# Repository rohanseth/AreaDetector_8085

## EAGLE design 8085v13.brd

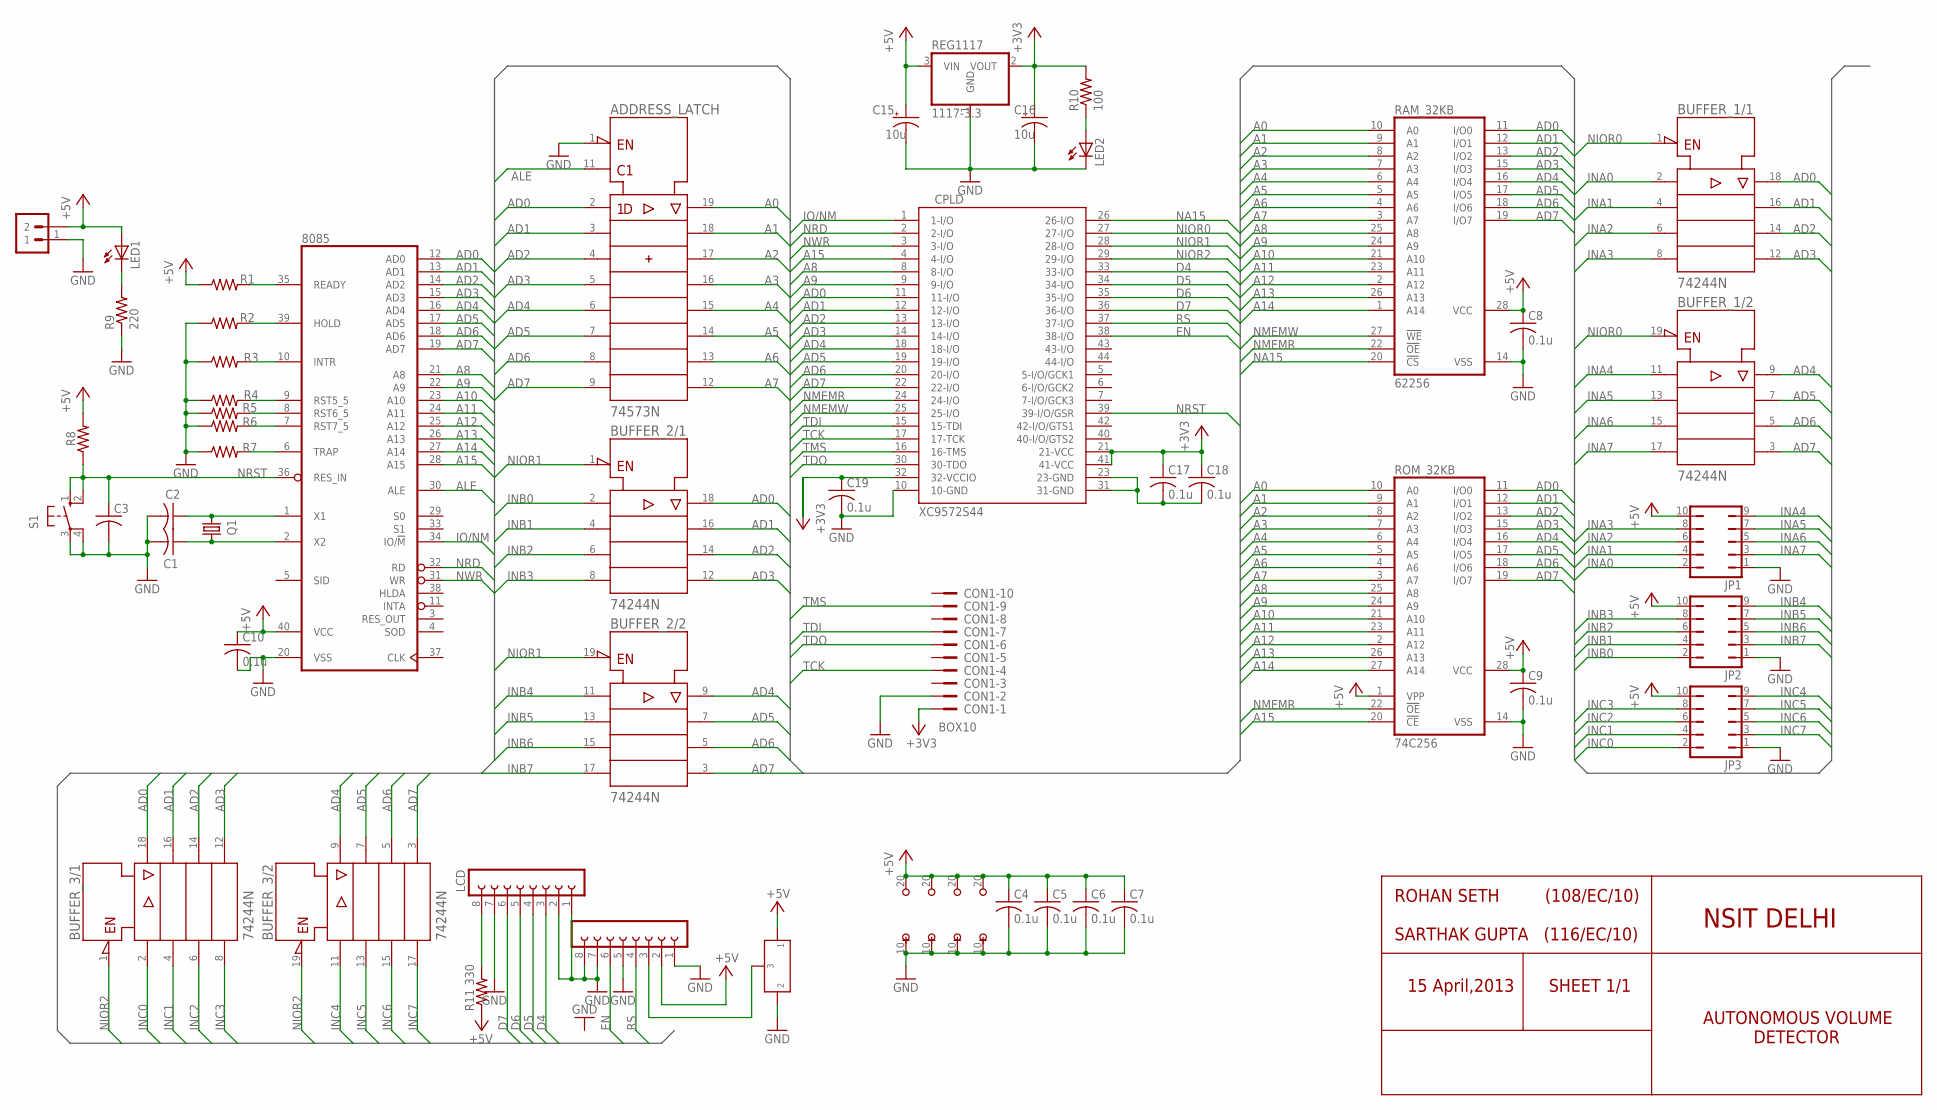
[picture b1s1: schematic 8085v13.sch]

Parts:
1117-3.3: REG1117; SOT223
8085: 8085; DIL40
ADDRESS_LATCH: 74573N; DIL20
BUFFER_1, BUFFER_2, BUFFER_3: 74244N; DIL20
C1, C2, C3: C-US025-030X050; C025-030X050
C4, C5, C6, C7, C8, C9, C10, C17, C18, C19: 0.1u; C025-030X050
C15, C16: 10u; E2,5-5
CON1: BOX10
CPLD: XC9572S44; PLCC-S44
JP1, JP2, JP3: JP5Q
LCD: FE08-1; FE08
LED1, LED2: LED3MM
Q1: CRYSTALHC49US; HC49US
R1, R2, R3, R4, R5, R6, R7, R8: R-US_0207/10; 0207/10
R9: 220; 0207/10
R10: 100; 0207/10
R11: 330; 0207/10
RAM_32KB: 62256; DIL28-6
ROM_32KB: 74C256; DIL28-6
S1: 10-XX; B3F-10XX
SV2: FE08-1; FE08
U$1: PRESET_LR
U$2: 1X2_LR

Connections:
+3V3: 1117-3.3.2 (VOUT), C16.+, C17.1, C18.1, C19.1, CON1.1, CPLD.21 (21-VCC), CPLD.32 (32-VCCIO), CPLD.41 (41-VCC), R10.2
+5V: 1117-3.3.3 (VIN), 8085.40 (VCC), ADDRESS_LATCH.20 (+UB), BUFFER_1.20 (+UB), BUFFER_2.20 (+UB), BUFFER_3.20 (+UB), C4.1, C5.1, C6.1, C7.1, C8.1, C9.1, C10.1, C15.+, JP1.10, JP2.10, JP3.10, LED1.A, R1.1, R8.2, R11.1, RAM_32KB.28 (VCC), ROM_32KB.1 (VPP), ROM_32KB.28 (VCC), SV2.2, U$1.P$1 (1), U$2.2
A0: ADDRESS_LATCH.19 (1Q), RAM_32KB.10 (A0), ROM_32KB.10 (A0)
A1: ADDRESS_LATCH.18 (2Q), RAM_32KB.9 (A1), ROM_32KB.9 (A1)
A2: ADDRESS_LATCH.17 (3Q), RAM_32KB.8 (A2), ROM_32KB.8 (A2)
A3: ADDRESS_LATCH.16 (4Q), RAM_32KB.7 (A3), ROM_32KB.7 (A3)
A4: ADDRESS_LATCH.15 (5Q), RAM_32KB.6 (A4), ROM_32KB.6 (A4)
A5: ADDRESS_LATCH.14 (6Q), RAM_32KB.5 (A5), ROM_32KB.5 (A5)
A6: ADDRESS_LATCH.13 (7Q), RAM_32KB.4 (A6), ROM_32KB.4 (A6)
A7: ADDRESS_LATCH.12 (8Q), RAM_32KB.3 (A7), ROM_32KB.3 (A7)
A8: 8085.21 (A8), CPLD.8 (8-I/O), RAM_32KB.25 (A8), ROM_32KB.25 (A8)
A9: 8085.22 (A9), CPLD.9 (9-I/O), RAM_32KB.24 (A9), ROM_32KB.24 (A9)
A10: 8085.23 (A10), RAM_32KB.21 (A10), ROM_32KB.21 (A10)
A11: 8085.24 (A11), RAM_32KB.23 (A11), ROM_32KB.23 (A11)
A12: 8085.25 (A12), RAM_32KB.2 (A12), ROM_32KB.2 (A12)
A13: 8085.26 (A13), RAM_32KB.26 (A13), ROM_32KB.26 (A13)
A14: 8085.27 (A14), RAM_32KB.1 (A14), ROM_32KB.27 (A14)
A15: 8085.28 (A15), CPLD.4 (4-I/O), ROM_32KB.20 (!CE)
AD0: 8085.12 (AD0), ADDRESS_LATCH.2 (1D), BUFFER_1.18 (Y1), BUFFER_2.18 (Y1), BUFFER_3.18 (Y1), CPLD.11 (11-I/O), RAM_32KB.11 (I/O0), ROM_32KB.11 (I/O0)
AD1: 8085.13 (AD1), ADDRESS_LATCH.3 (2D), BUFFER_1.16 (Y2), BUFFER_2.16 (Y2), BUFFER_3.16 (Y2), CPLD.12 (12-I/O), RAM_32KB.12 (I/O1), ROM_32KB.12 (I/O1)
AD2: 8085.14 (AD2), ADDRESS_LATCH.4 (3D), BUFFER_1.14 (Y3), BUFFER_2.14 (Y3), BUFFER_3.14 (Y3), CPLD.13 (13-I/O), RAM_32KB.13 (I/O2), ROM_32KB.13 (I/O2)
AD3: 8085.15 (AD3), ADDRESS_LATCH.5 (4D), BUFFER_1.12 (Y4), BUFFER_2.12 (Y4), BUFFER_3.12 (Y4), CPLD.14 (14-I/O), RAM_32KB.15 (I/O3), ROM_32KB.15 (I/O3)
AD4: 8085.16 (AD4), ADDRESS_LATCH.6 (5D), BUFFER_1.9 (Y1), BUFFER_2.9 (Y1), BUFFER_3.9 (Y1), CPLD.18 (18-I/O), RAM_32KB.16 (I/O4), ROM_32KB.16 (I/O4)
AD5: 8085.17 (AD5), ADDRESS_LATCH.7 (6D), BUFFER_1.7 (Y2), BUFFER_2.7 (Y2), BUFFER_3.7 (Y2), CPLD.19 (19-I/O), RAM_32KB.17 (I/O5), ROM_32KB.17 (I/O5)
AD6: 8085.18 (AD6), ADDRESS_LATCH.8 (7D), BUFFER_1.5 (Y3), BUFFER_2.5 (Y3), BUFFER_3.5 (Y3), CPLD.20 (20-I/O), RAM_32KB.18 (I/O6), ROM_32KB.18 (I/O6)
AD7: 8085.19 (AD7), ADDRESS_LATCH.9 (8D), BUFFER_1.3 (Y4), BUFFER_2.3 (Y4), BUFFER_3.3 (Y4), CPLD.22 (22-I/O), RAM_32KB.19 (I/O7), ROM_32KB.19 (I/O7)
ALE: 8085.30 (ALE), ADDRESS_LATCH.11 (C)
D4: CPLD.33 (33-I/O), LCD.3
D5: CPLD.34 (34-I/O), LCD.4
D6: CPLD.35 (35-I/O), LCD.5
D7: CPLD.36 (36-I/O), LCD.6
EN: CPLD.38 (38-I/O), SV2.6
GND: 1117-3.3.1 (GND), 8085.20 (VSS), ADDRESS_LATCH.1 (!OC), ADDRESS_LATCH.10 (-UB), BUFFER_1.10 (-UB), BUFFER_2.10 (-UB), BUFFER_3.10 (-UB), C1.2, C2.2, C3.2, C4.2, C5.2, C6.2, C7.2, C8.2, C9.2, C10.2, C15.-, C16.-, C19.2, CON1.2, CPLD.10 (10-GND), JP1.1, JP2.1, JP3.1, LCD.1, LCD.2, LCD.7, LED2.K (C), R2.1, R3.1, R4.1, R5.1, R6.1, R7.1, R9.1, RAM_32KB.14 (VSS), ROM_32KB.14 (VSS), S1.3, S1.4 (P1), SV2.1, SV2.5, SV2.7, SV2.8, U$1.P$2 (2), U$2.1
INA0: BUFFER_1.2 (A1), JP1.2
INA1: BUFFER_1.4 (A2), JP1.4
INA2: BUFFER_1.6 (A3), JP1.6
INA3: BUFFER_1.8 (A4), JP1.8
INA4: BUFFER_1.11 (A1), JP1.9
INA5: BUFFER_1.13 (A2), JP1.7
INA6: BUFFER_1.15 (A3), JP1.5
INA7: BUFFER_1.17 (A4), JP1.3
INB0: BUFFER_2.2 (A1), JP2.2
INB1: BUFFER_2.4 (A2), JP2.4
INB2: BUFFER_2.6 (A3), JP2.6
INB3: BUFFER_2.8 (A4), JP2.8
INB4: BUFFER_2.11 (A1), JP2.9
INB5: BUFFER_2.13 (A2), JP2.7
INB6: BUFFER_2.15 (A3), JP2.5
INB7: BUFFER_2.17 (A4), JP2.3
INC0: BUFFER_3.2 (A1), JP3.2
INC1: BUFFER_3.4 (A2), JP3.4
INC2: BUFFER_3.6 (A3), JP3.6
INC3: BUFFER_3.8 (A4), JP3.8
INC4: BUFFER_3.11 (A1), JP3.9
INC5: BUFFER_3.13 (A2), JP3.7
INC6: BUFFER_3.15 (A3), JP3.5
INC7: BUFFER_3.17 (A4), JP3.3
IO/NM: 8085.34 (IO/!M), CPLD.1 (1-I/O)
unnamed: 8085.1 (X1), C2.1, Q1.2
unnamed: 8085.2 (X2), C1.1, Q1.1
unnamed: 8085.35 (READY), R1.2
unnamed: 8085.39 (HOLD), R2.2
unnamed: 8085.10 (INTR), R3.2
unnamed: 8085.9 (RST5_5), R4.2
unnamed: 8085.8 (RST6_5), R5.2
unnamed: 8085.7 (RST7_5), R6.2
unnamed: 8085.6 (TRAP), R7.2
unnamed: C17.2, C18.2, CPLD.23 (23-GND), CPLD.31 (31-GND)
unnamed: LCD.8, R11.2
unnamed: LED1.K (C), R9.2
unnamed: SV2.3, U$1.P$3 (3)
unnamed: LED2.A, R10.1
NA15: CPLD.26 (26-I/O), RAM_32KB.20 (!CS)
NIOR0: BUFFER_1.1 (!G), BUFFER_1.19 (!G), CPLD.27 (27-I/O)
NIOR1: BUFFER_2.1 (!G), BUFFER_2.19 (!G), CPLD.28 (28-I/O)
NIOR2: BUFFER_3.1 (!G), BUFFER_3.19 (!G), CPLD.29 (29-I/O)
NMEMR: CPLD.24 (24-I/O), RAM_32KB.22 (!OE), ROM_32KB.22 (!OE)
NMEMW: CPLD.25 (25-I/O), RAM_32KB.27 (!WE)
NRD: 8085.32 (RD), CPLD.2 (2-I/O)
NRST: 8085.36 (RES_IN), C3.1, CPLD.39 (39-I/O/GSR), R8.1, S1.1 (S), S1.2 (S1)
NWR: 8085.31 (WR), CPLD.3 (3-I/O)
RS: CPLD.37 (37-I/O), SV2.4
TCK: CON1.4, CPLD.17 (17-TCK)
TDI: CON1.7, CPLD.15 (15-TDI)
TDO: CON1.6, CPLD.30 (30-TDO)
TMS: CON1.9, CPLD.16 (16-TMS)

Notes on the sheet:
ROHAN SETH (108/EC/10) SARTHAK GUPTA (116/EC/10)
NSIT DELHI
SHEET 1/1
15 April,2013
AUTONOMOUS VOLUME DETECTOR

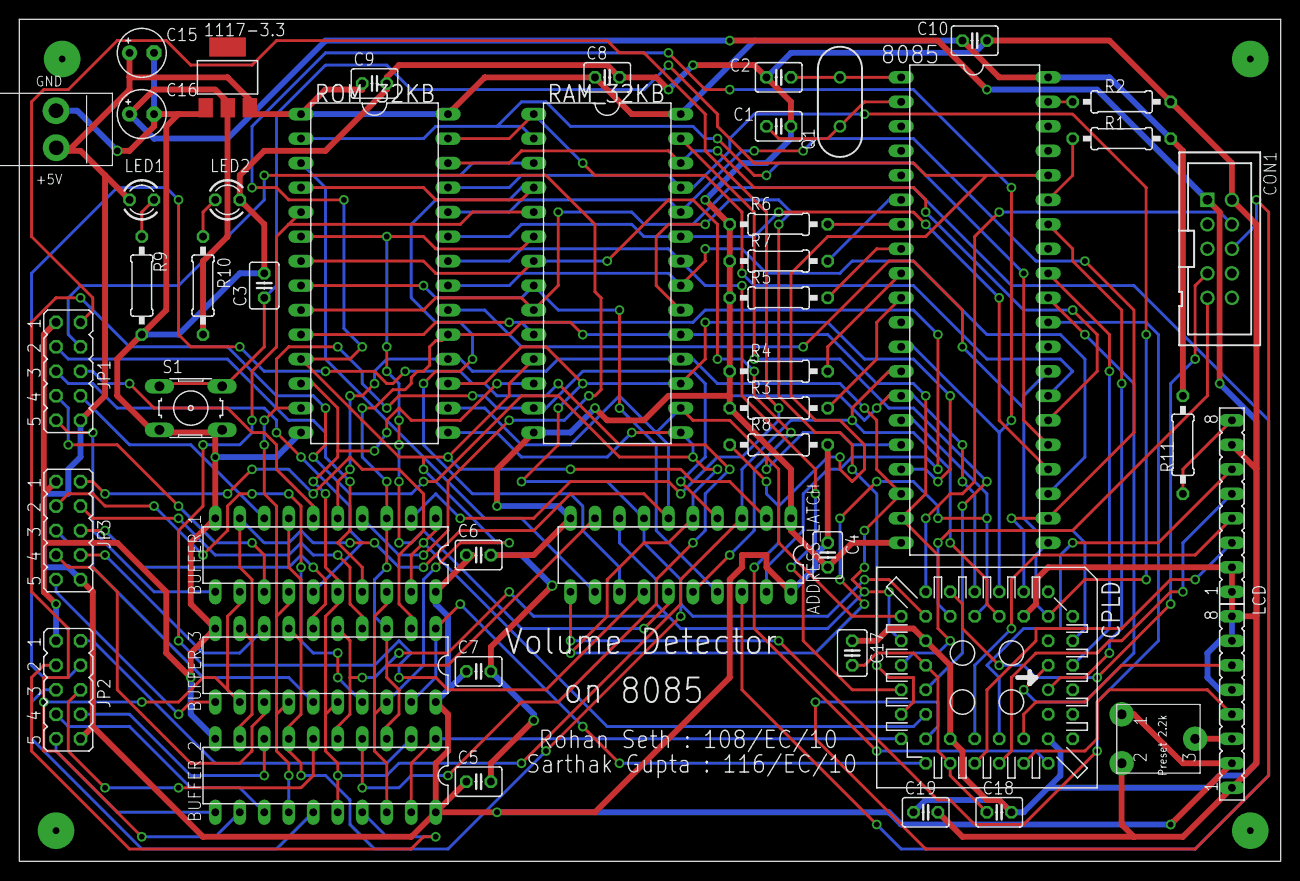
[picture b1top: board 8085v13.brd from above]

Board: 2 copper layers, 130.8 x 87.3 mm, 47 parts (0 on the bottom side), 86 nets.

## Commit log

2013-07-19 Files Added

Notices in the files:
parts and their libraries:
sparkfun: Licensing: CC v3.0 Share-Alike You are welcome to use this library for commercial purposes.
